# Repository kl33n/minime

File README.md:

# minime

3D printer mainboard Minime + Minime_mini, using a Raspberry Pi Pico (RP2040). Can be used on top of a Raspberry Pi or as standalone USB version.

The main goal of creating this little board was to design a 3D printer mainboard with Raspberry Pi Pico (RP2040) as MCU running Klipper firmware. Because of the limited number of I/O pins and ADC pins the board results in a very minimalistic (only 4 Stepper Driver on minime_mini) but also universal PCB.

Main Features:
- Running Klipper Firmware on Raspberry Pi Pico
- Raspberry Pi Host Version = use the minime and minime_mini as 3D Printer Mainboard with all primary features, like Heat_Bed and Hotend Control, Hotend Fan and Part Fan Control, X/Y/Z Endstop reading, Hotend Temperature and Bed Temperature reading, Probe reading, controlling 4 TMC2209 Stepper Driver
- The minime board can separately be used as standalone sensor board without the need of minime_mini as driver board and can directly be connected via usb to any Raspberry Pi Host
- Switchable between Endswitch and sensorless Homing via Solderjumper
- Switchable between +5V and +24V Probe via Solderjumper
- Switchable between +5V and +24V Fan Supply via Solderjumper
- Hotend Fan (Fan1, Sunon MF40100V1-1000C-G99) uses a 3 pin Header: VCC, GND and tachometer signal for savety reasons
- Fan tachometer signal can be set up in Klipper. If the speed of the Hotend Fan is not detectable, Klipper shuts down the printer (future option)
- Integrated bat85 diode (or similar) if using +24V probe
- Raspberry Pi Pico is used with pin headers to completely exchange the module if broken

Raspberry Pi Pico (with RP2040 Microcontroller):

- Raspberry Pi Host Version --> Raspberry Pi Pico has to be flashed with klipper.uf2 (UART Communication Option)
- Raspberry Pi Pico standalone Version --> Raspberry Pi Pico has to be flashed with klipper.uf2 (USB Communication Option)

A special thanks goes to Matt Shepcar (https://easyeda.com/matt_1626/) for his inspiring projects "Piglet print head control board" and "Raspberry Pi G-Code HAT"!

Future Modification:
- Switch from Raspberry Pi Pico Module to RP2040 integrated circuit
- Design two RP2040 MCU board, a host version with more than 4 stepper driver as driverboard and a separat sensorboard version including endswitches/hotend/bed/fans/temperatursensors and much more

Has to be continued!

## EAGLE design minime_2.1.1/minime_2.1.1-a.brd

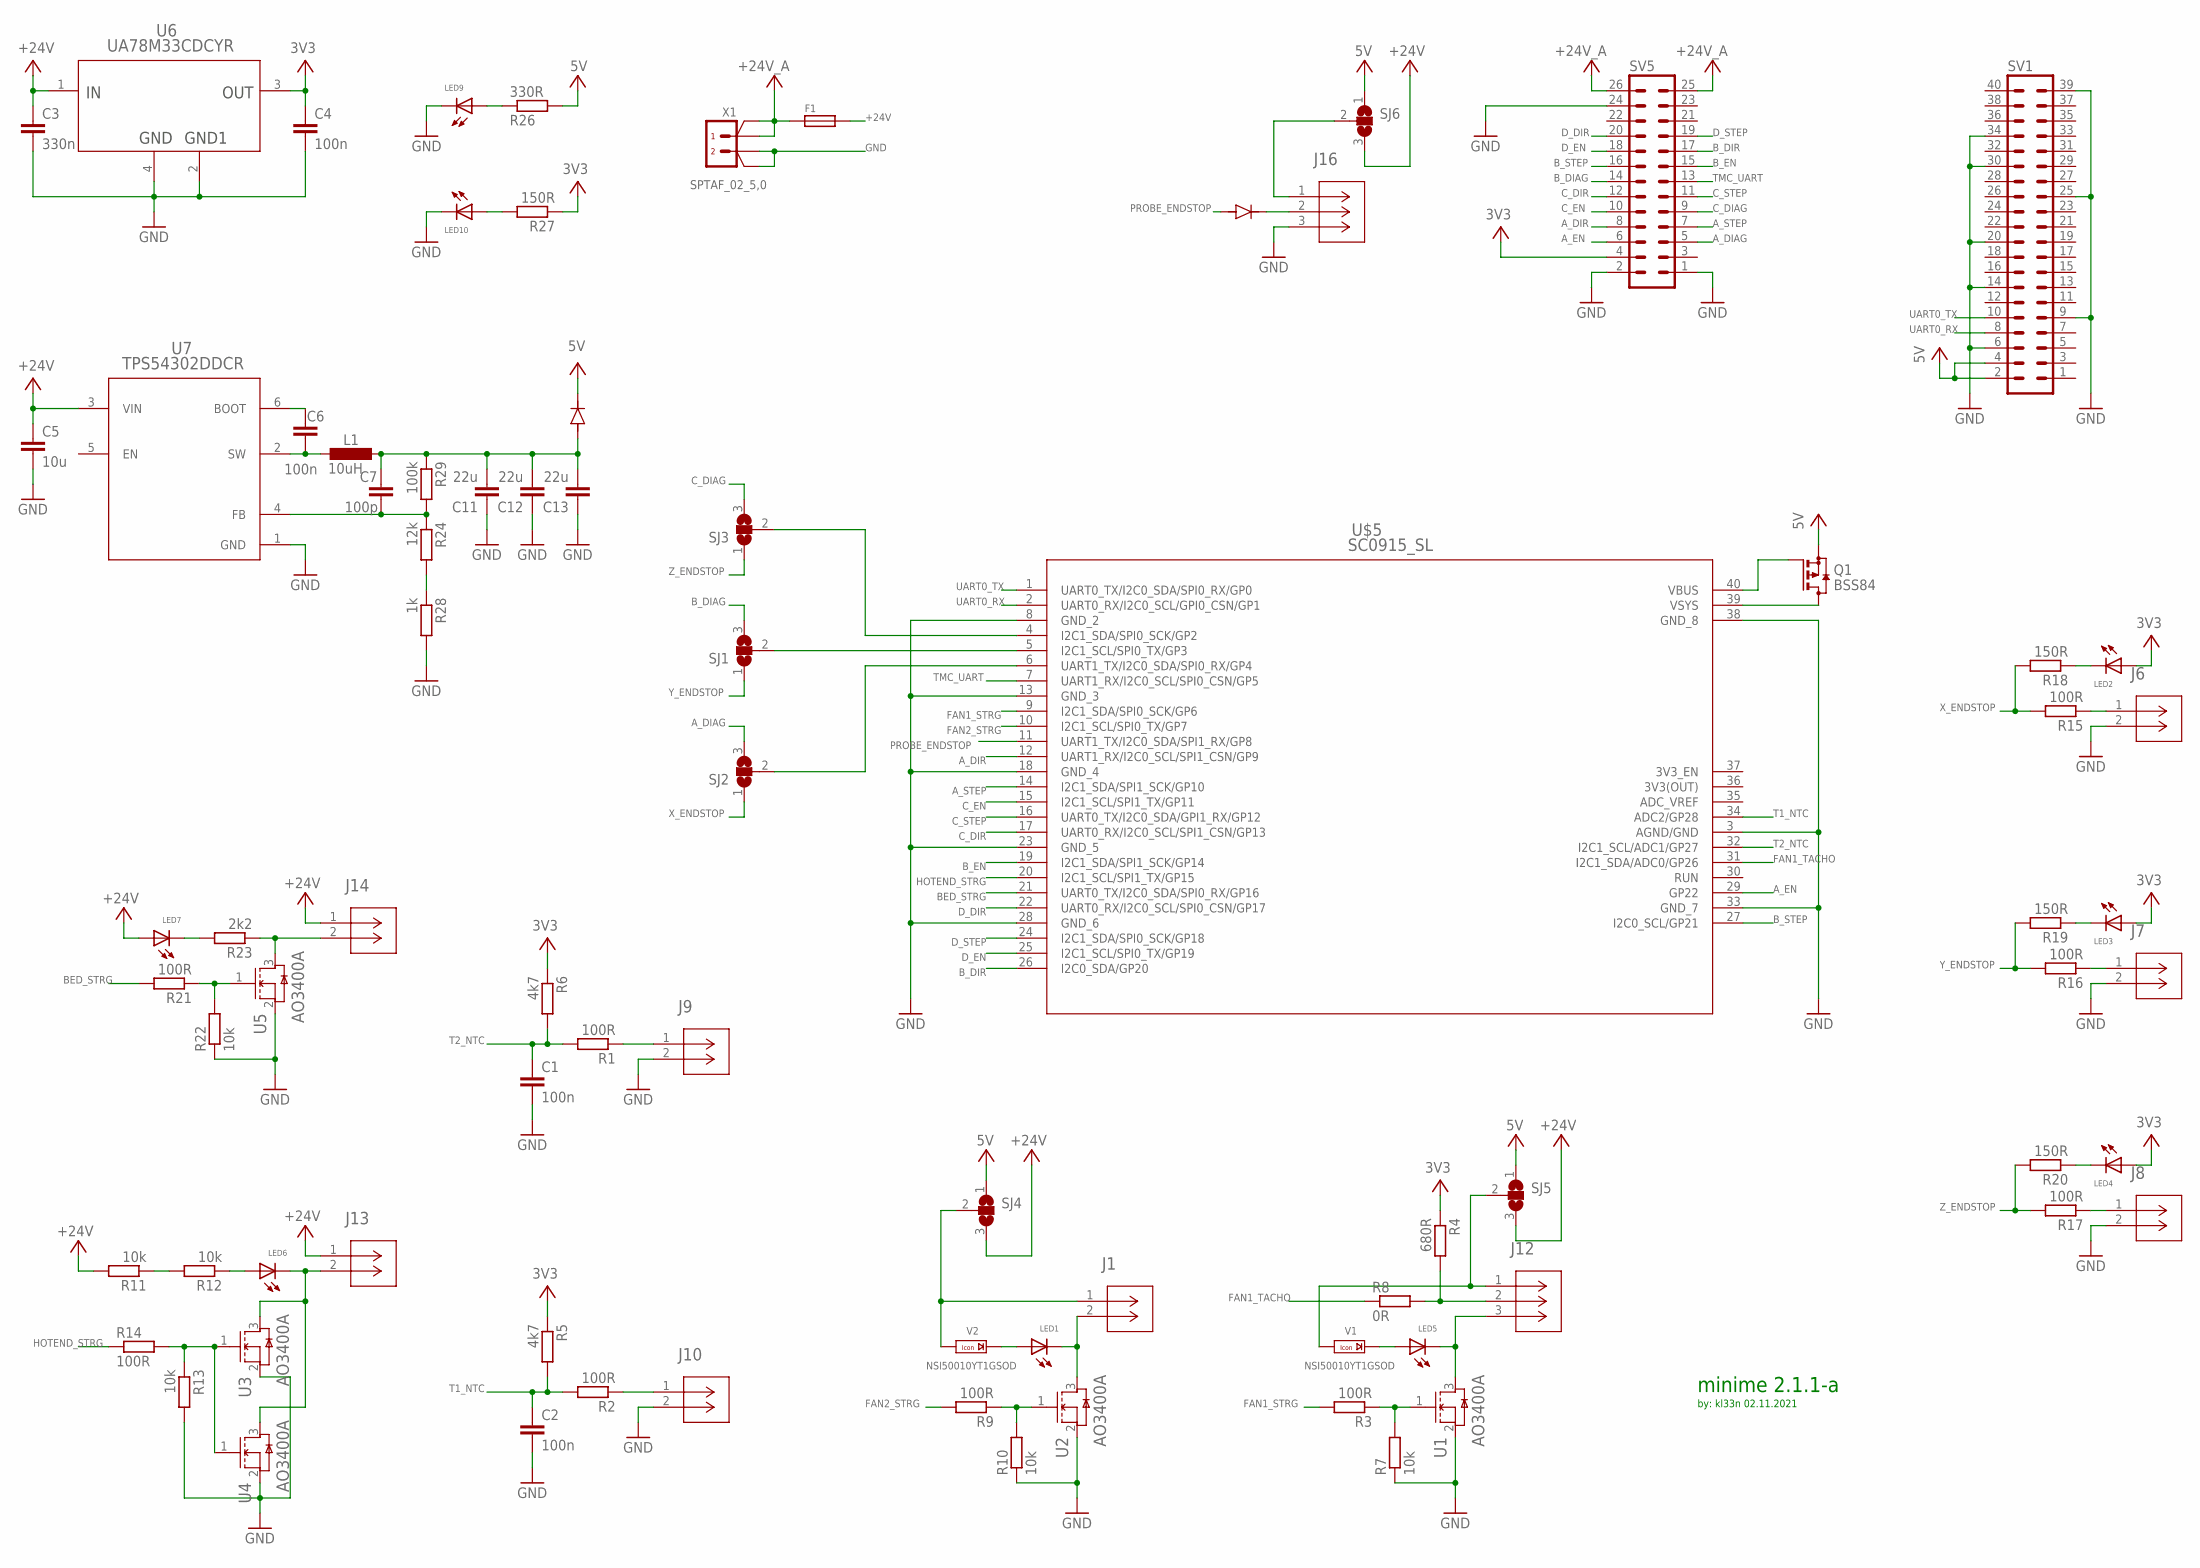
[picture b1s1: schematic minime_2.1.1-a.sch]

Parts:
C1, C2, C4, C6: 100n; C0603
C3: 330n; C0603
C5: 10u; C0603
C7: 100p; C0603
C11, C12, C13: 22u; C1210K
CR1: SS54; DIODE_DO214AC
CR2: SS14; DIODE_DO214AC
F1: FUSE/SERIE154; FUSE/NANO-OMNI
J1, J6, J7, J8, J9, J10, J13, J14: B2B-XH-A(LF)(SN); CONN_B2B-XH-A(LF)(SN)_JST
J12, J16: B3B-XH-A(LF)(SN); CONN_B3B-XH-A_JST
L1: 10uH; POWER-CHOKE_WE-TPC
LED1, LED2, LED3, LED4, LED5, LED6, LED7, LED9, LED10: LEDCHIP-LED0603; CHIP-LED0603
Q1: BSS84; SOT23
R1, R2, R3, R9, R14, R15, R16, R17, R21: 100R; R0603
R4: 680R; R0603
R5, R6: 4k7; R0603
R7, R10, R11, R12, R13, R22: 10k; R0603
R8: 0R; R0603
R18, R19, R20, R27: 150R; R0603
R23: 2k2; R0603
R24: 12k; R0603
R26: 330R; R0603
R28: 1k; R0603
R29: 100k; R0603
SJ1, SJ2, SJ3, SJ4, SJ5, SJ6: SJ2W; SJ_2
SV1: MA20-2
SV5: MA13-2
U1, U2, U3, U4, U5: AO3400A; SOT-23-3L_AOS
U6: UA78M33CDCYR; DCY0004A_N
U7: TPS54302DDCR; DDC0006A_N
U$5: SC0915_SL; STIFTLEISTE
V1, V2: NSI50010YT1GSOD; SOD123
X1: SPTAF_02_5,0; 5-2

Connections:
3V3: C4.1, LED2.A, LED3.A, LED4.A, R4.1, R5.1, R6.1, R27.1, SV5.4, U6.3 (OUTPUT)
3V3_EN: U$5.37 (3V3_EN)
5V: CR1.1, Q1.2 (S), R26.2, SJ4.1, SJ5.1, SJ6.1, SV1.2, SV1.4
+24V: C3.1, C5.1, F1.2, J13.1, J14.1, LED7.A, R11.2, SJ4.3, SJ5.3, SJ6.3, U6.1 (INPUT), U7.3 (VIN)
+24V_A: F1.1, SV5.25, SV5.26, X1.1, X1.1A
ADC_VREF: U$5.35 (ADC_VREF)
A_DIAG: SJ2.3, SV5.5
A_DIAG_X_ENDSTOP: SJ2.2, U$5.6 (UART1_TX/I2C0_SDA/SPI0_RX/GP4)
A_DIR: SV5.8, U$5.12 (UART1_RX/I2C0_SCL/SPI1_CSN/GP9)
A_EN: SV5.6, U$5.29 (GP22)
A_STEP: SV5.7, U$5.14 (I2C1_SDA/SPI1_SCK/GP10)
BED_STRG: R21.2, U$5.21 (UART0_TX/I2C0_SDA/SPI0_RX/GP16)
B_DIAG: SJ1.3, SV5.14
B_DIAG_Y_ENDSTOP: SJ1.2, U$5.5 (I2C1_SCL/SPI0_TX/GP3)
B_DIR: SV5.17, U$5.26 (I2C0_SDA/GP20)
B_EN: SV5.15, U$5.19 (I2C1_SDA/SPI1_SCK/GP14)
B_STEP: SV5.16, U$5.27 (I2C0_SCL/GP21)
C_DIAG: SJ3.3, SV5.9
C_DIAG_Z_ENDSTOP: SJ3.2, U$5.4 (I2C1_SDA/SPI0_SCK/GP2)
C_DIR: SV5.12, U$5.17 (UART0_RX/I2C0_SCL/SPI1_CSN/GP13)
C_EN: SV5.10, U$5.15 (I2C1_SCL/SPI1_TX/GP11)
C_STEP: SV5.11, U$5.16 (UART0_TX/I2C0_SDA/GPI1_RX/GP12)
D_DIR: SV5.20, U$5.22 (UART0_RX/I2C0_SCL/SPI0_CSN/GP17)
D_EN: SV5.18, U$5.25 (I2C1_SCL/SPI0_TX/GP19)
D_STEP: SV5.19, U$5.24 (I2C1_SDA/SPI0_SCK/GP18)
FAN1_STRG: R3.2, U$5.9 (I2C1_SDA/SPI0_SCK/GP6)
FAN1_TACHO: R8.1, U$5.31 (I2C1_SDA/ADC0/GP26)
FAN2_STRG: R9.2, U$5.10 (I2C1_SCL/SPI0_TX/GP7)
GND: C1.2, C2.2, C3.2, C4.2, C5.2, C11.1, C12.1, C13.1, J6.2, J7.2, J8.2, J9.2, J10.2, J16.3, LED9.C, LED10.C, R7.1, R10.1, R13.2, R22.1, R28.2, SV1.6, SV1.9, SV1.14, SV1.20, SV1.25, SV1.30, SV1.34, SV1.39, SV5.1, SV5.2, SV5.24, U1.2 (S), U2.2 (S), U3.2 (S), U4.2 (S), U5.2 (S), U6.2 (COMMON_2), U6.4 (COMMON), U7.1 (GND), U$5.3 (AGND/GND), U$5.8 (GND_2), U$5.13 (GND_3), U$5.18 (GND_4), U$5.23 (GND_5), U$5.28 (GND_6), U$5.33 (GND_7), U$5.38 (GND_8), X1.2, X1.2A
HOTEND_STRG: R14.1, U$5.20 (I2C1_SCL/SPI1_TX/GP15)
unnamed: LED6.A, R12.1
unnamed: R11.1, R12.2
unnamed: R21.1, R22.2, U5.1 (G)
unnamed: R13.1, R14.2, U3.1 (G), U4.1 (G)
unnamed: J16.1, SJ6.2
unnamed: LED5.A, V1.C (K)
unnamed: R9.1, R10.2, U2.1 (G)
unnamed: LED1.A, V2.C (K)
unnamed: J14.2, R23.1, U5.3 (D)
unnamed: J1.2, LED1.C, U2.3 (D)
unnamed: J8.1, R17.1
unnamed: J7.1, R16.1
unnamed: J6.1, R15.1
unnamed: J10.1, R2.1
unnamed: LED2.C, R18.1
unnamed: LED3.C, R19.1
unnamed: J9.1, R1.1
unnamed: J12.2, R4.2, R8.2
unnamed: LED4.C, R20.1
unnamed: R3.1, R7.2, U1.1 (G)
unnamed: LED7.C, R23.2
unnamed: J12.3, LED5.C, U1.3 (D)
unnamed: J13.2, LED6.C, U3.3 (D), U4.3 (D)
unnamed: LED9.A, R26.1
unnamed: J12.1, SJ5.2, V1.A
unnamed: LED10.A, R27.2
unnamed: J1.1, SJ4.2, V2.A
unnamed: CR2.1, J16.2
unnamed: R24.2, R28.1
unnamed: C6.1, U7.6 (BOOT)
unnamed: C6.2, L1.2, U7.2 (SW)
unnamed: C7.2, R24.1, R29.2, U7.4 (FB)
unnamed: C7.1, C11.2, C12.2, C13.2, CR1.2, L1.1, R29.1
PROBE_ENDSTOP: CR2.2, U$5.11 (UART1_TX/I2C0_SDA/SPI1_RX/GP8)
T1_NTC: C2.1, R2.2, R5.2, U$5.34 (ADC2/GP28)
T2_NTC: C1.1, R1.2, R6.2, U$5.32 (I2C1_SCL/ADC1/GP27)
TMC_UART: SV5.13, U$5.7 (UART1_RX/I2C0_SCL/SPI0_CSN/GP5)
UART0_RX: SV1.8, U$5.2 (UART0_RX/I2C0_SCL/GPI0_CSN/GP1)
UART0_TX: SV1.10, U$5.1 (UART0_TX/I2C0_SDA/SPI0_RX/GP0)
VBUS: Q1.1 (G), U$5.40 (VBUS)
VSYS: Q1.3 (D), U$5.39 (VSYS)
X_ENDSTOP: R15.2, R18.2, SJ2.1
Y_ENDSTOP: R16.2, R19.2, SJ1.1
Z_ENDSTOP: R17.2, R20.2, SJ3.1

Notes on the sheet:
by: kl33n 02.11.2021
minime 2.1.1-a

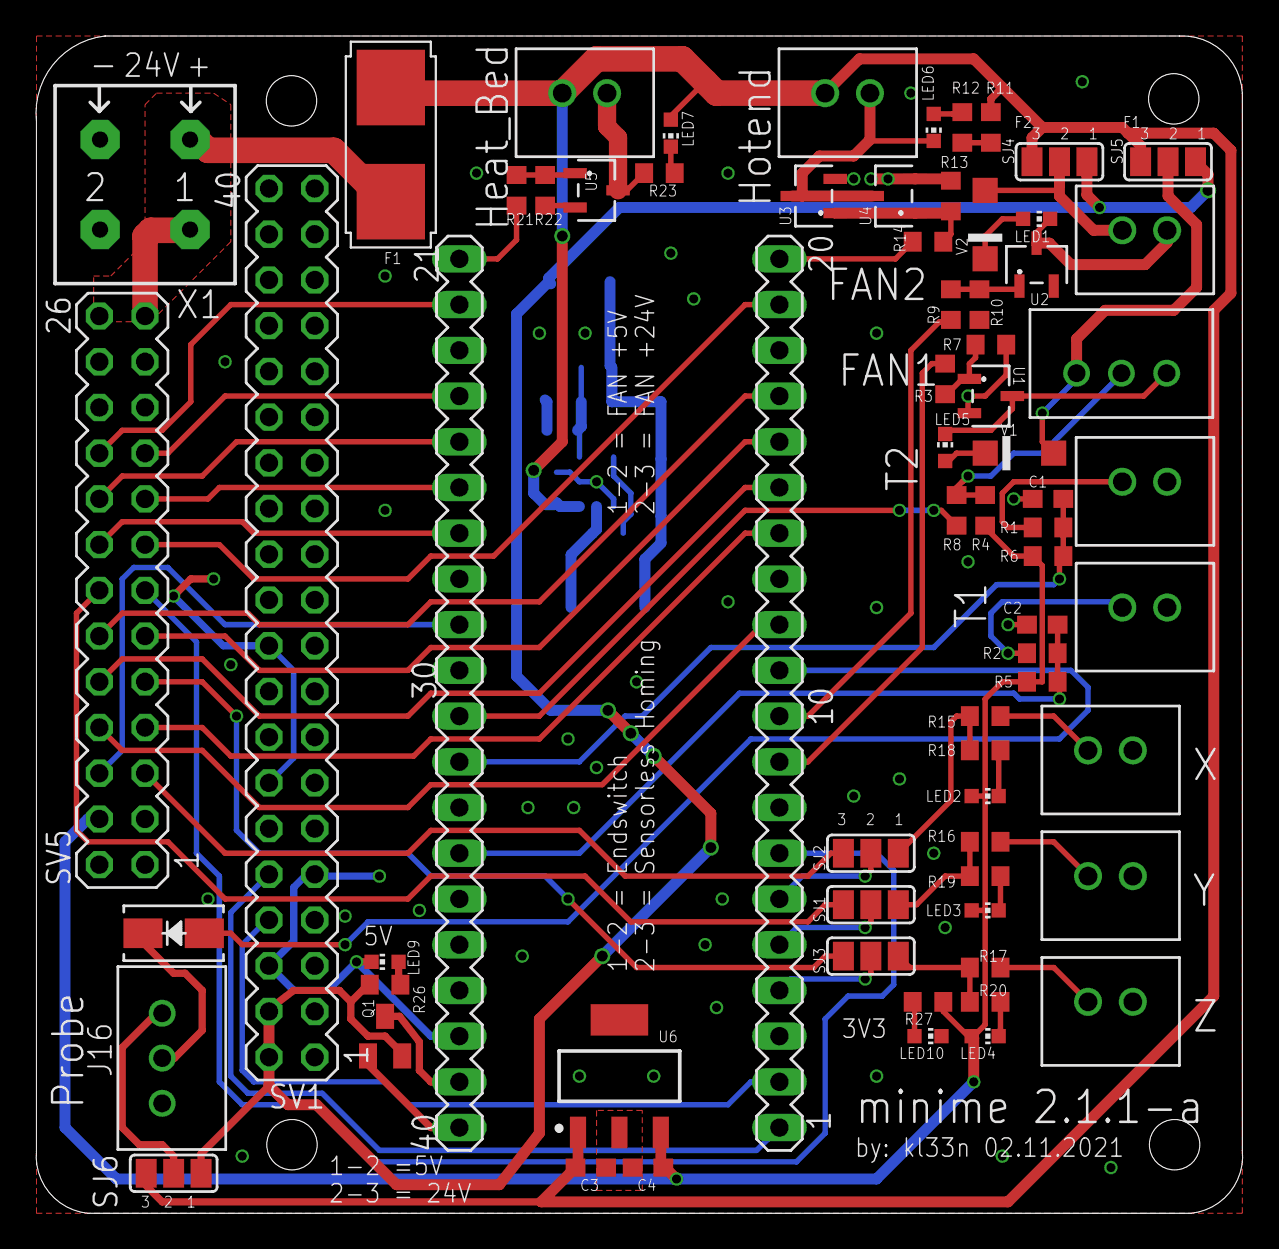
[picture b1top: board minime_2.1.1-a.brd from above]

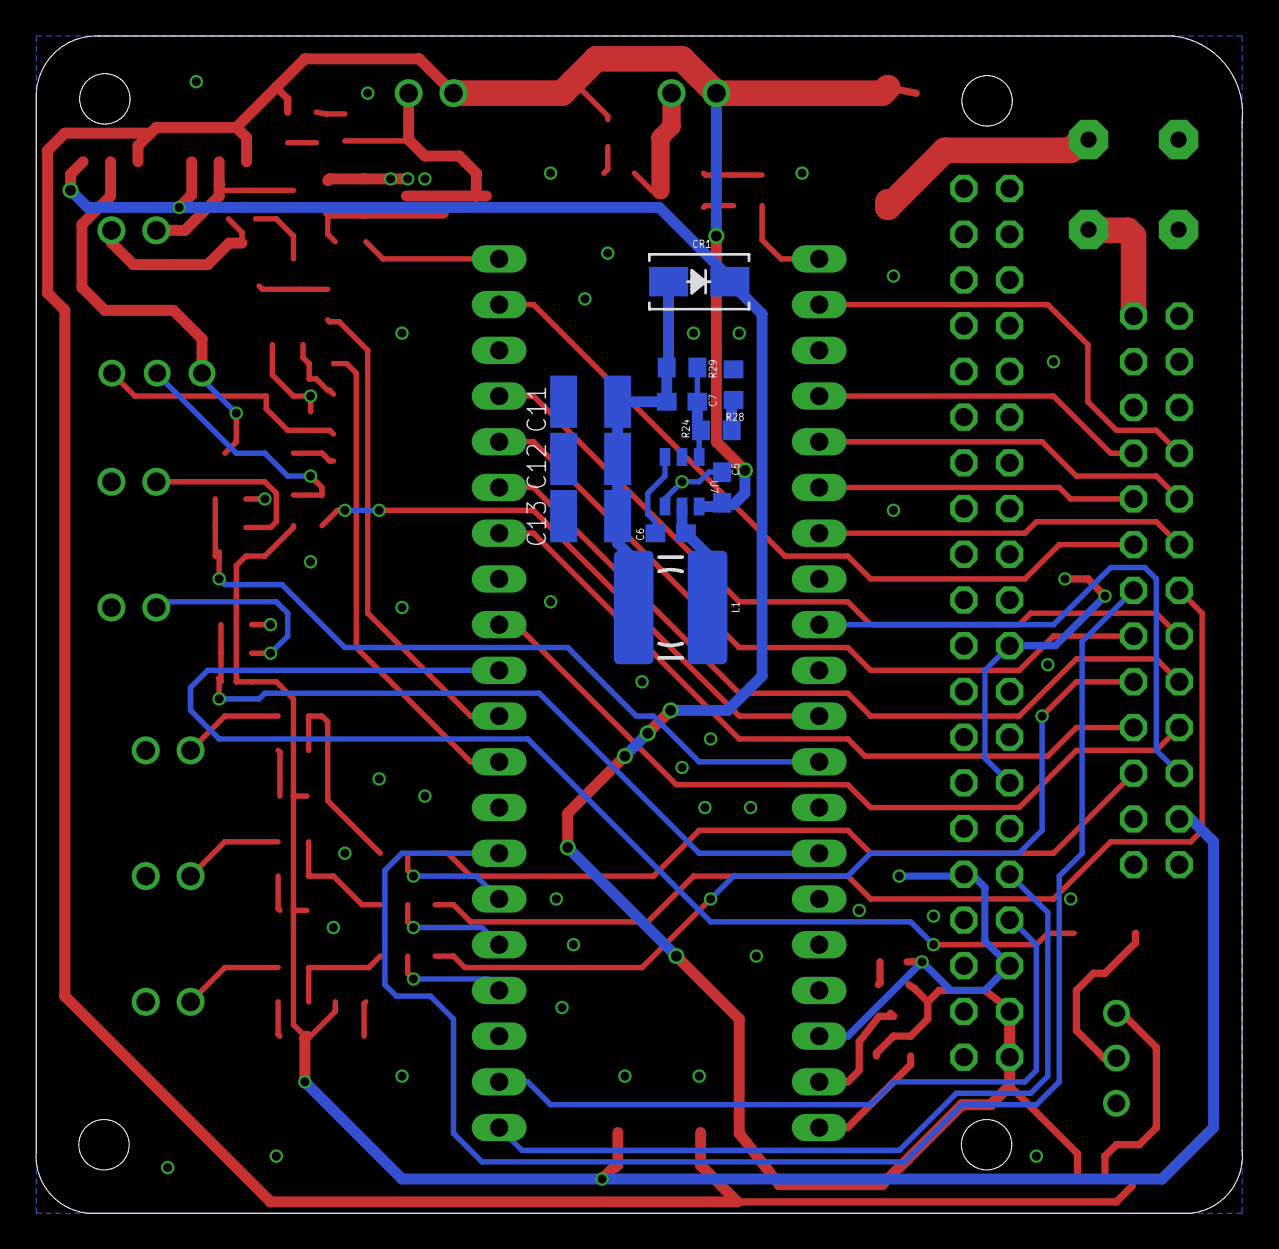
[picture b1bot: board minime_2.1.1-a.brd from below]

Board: 2 copper layers, 67.0 x 65.4 mm, 81 parts (12 on the bottom side), 72 nets.

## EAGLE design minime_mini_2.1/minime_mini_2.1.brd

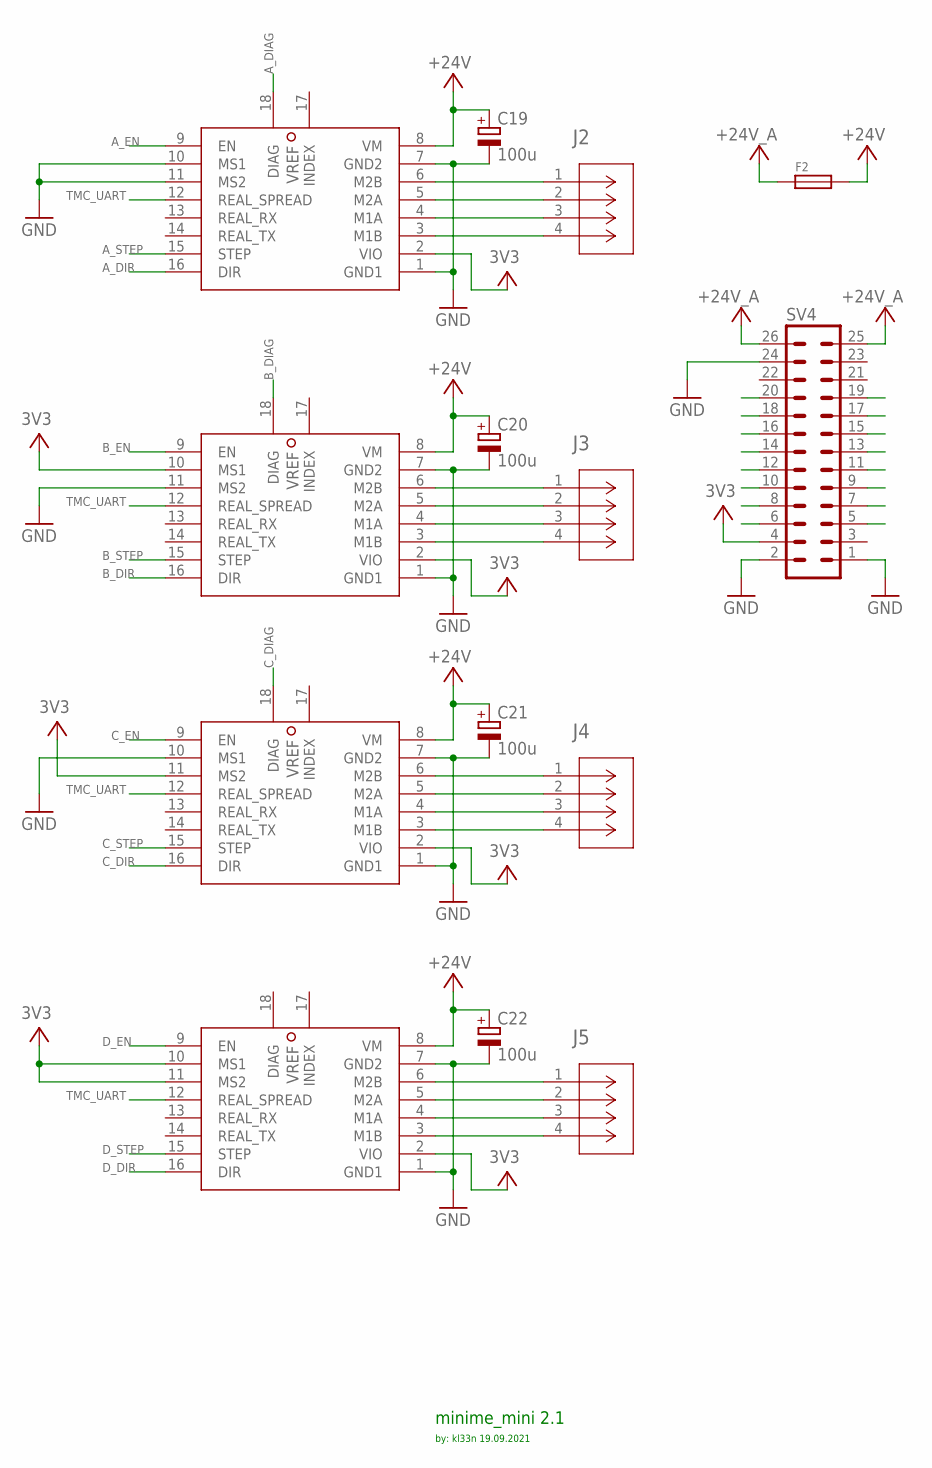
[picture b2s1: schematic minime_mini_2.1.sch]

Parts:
C19, C20, C21, C22: 100u; 175TMP-0810
F2: FUSE/SERIE154; FUSE/NANO-OMNI
J2, J3, J4, J5: B4B-XH-AM(LF)(SN); CONN_B4B-XH-AM_JST
SV4: MA13-2
U$1, U$2, U$3, U$4: TMC2209

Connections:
3V3: SV4.4, U$1.2 (VIO), U$1.10 (MS1), U$2.2 (VIO), U$3.2 (VIO), U$3.11 (MS2), U$4.2 (VIO), U$4.10 (MS1), U$4.11 (MS2)
+24V: C19.+, C20.+, C21.+, C22.+, F2.2, U$1.8 (VM), U$2.8 (VM), U$3.8 (VM), U$4.8 (VM)
+24V_A: F2.1, SV4.25, SV4.26
A_DIAG: SV4.5, U$2.18 (DIAG)
A_DIR: SV4.8, U$2.16 (DIR)
A_EN: SV4.6, U$2.9 (EN)
A_STEP: SV4.7, U$2.15 (STEP)
B_DIAG: SV4.14, U$1.18 (DIAG)
B_DIR: SV4.17, U$1.16 (DIR)
B_EN: SV4.15, U$1.9 (EN)
B_STEP: SV4.16, U$1.15 (STEP)
C_DIAG: SV4.9, U$3.18 (DIAG)
C_DIR: SV4.12, U$3.16 (DIR)
C_EN: SV4.10, U$3.9 (EN)
C_STEP: SV4.11, U$3.15 (STEP)
D_DIR: SV4.20, U$4.16 (DIR)
D_EN: SV4.18, U$4.9 (EN)
D_STEP: SV4.19, U$4.15 (STEP)
GND: C19.-, C20.-, C21.-, C22.-, SV4.1, SV4.2, SV4.24, U$1.1 (GND1), U$1.7 (GND2), U$1.11 (MS2), U$2.1 (GND1), U$2.7 (GND2), U$2.10 (MS1), U$2.11 (MS2), U$3.1 (GND1), U$3.7 (GND2), U$3.10 (MS1), U$4.1 (GND1), U$4.7 (GND2)
unnamed: J2.1, U$2.6 (M2B)
unnamed: J2.2, U$2.5 (M2A)
unnamed: J2.3, U$2.4 (M1A)
unnamed: J2.4, U$2.3 (M1B)
unnamed: J3.1, U$1.6 (M2B)
unnamed: J3.2, U$1.5 (M2A)
unnamed: J3.3, U$1.4 (M1A)
unnamed: J3.4, U$1.3 (M1B)
unnamed: J4.1, U$3.6 (M2B)
unnamed: J4.2, U$3.5 (M2A)
unnamed: J4.3, U$3.4 (M1A)
unnamed: J4.4, U$3.3 (M1B)
unnamed: J5.1, U$4.6 (M2B)
unnamed: J5.2, U$4.5 (M2A)
unnamed: J5.3, U$4.4 (M1A)
unnamed: J5.4, U$4.3 (M1B)
TMC_UART: SV4.13, U$1.12 (REAL_SPREAD), U$2.12 (REAL_SPREAD), U$3.12 (REAL_SPREAD), U$4.12 (REAL_SPREAD)

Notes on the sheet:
by: kl33n 19.09.2021
minime_mini 2.1

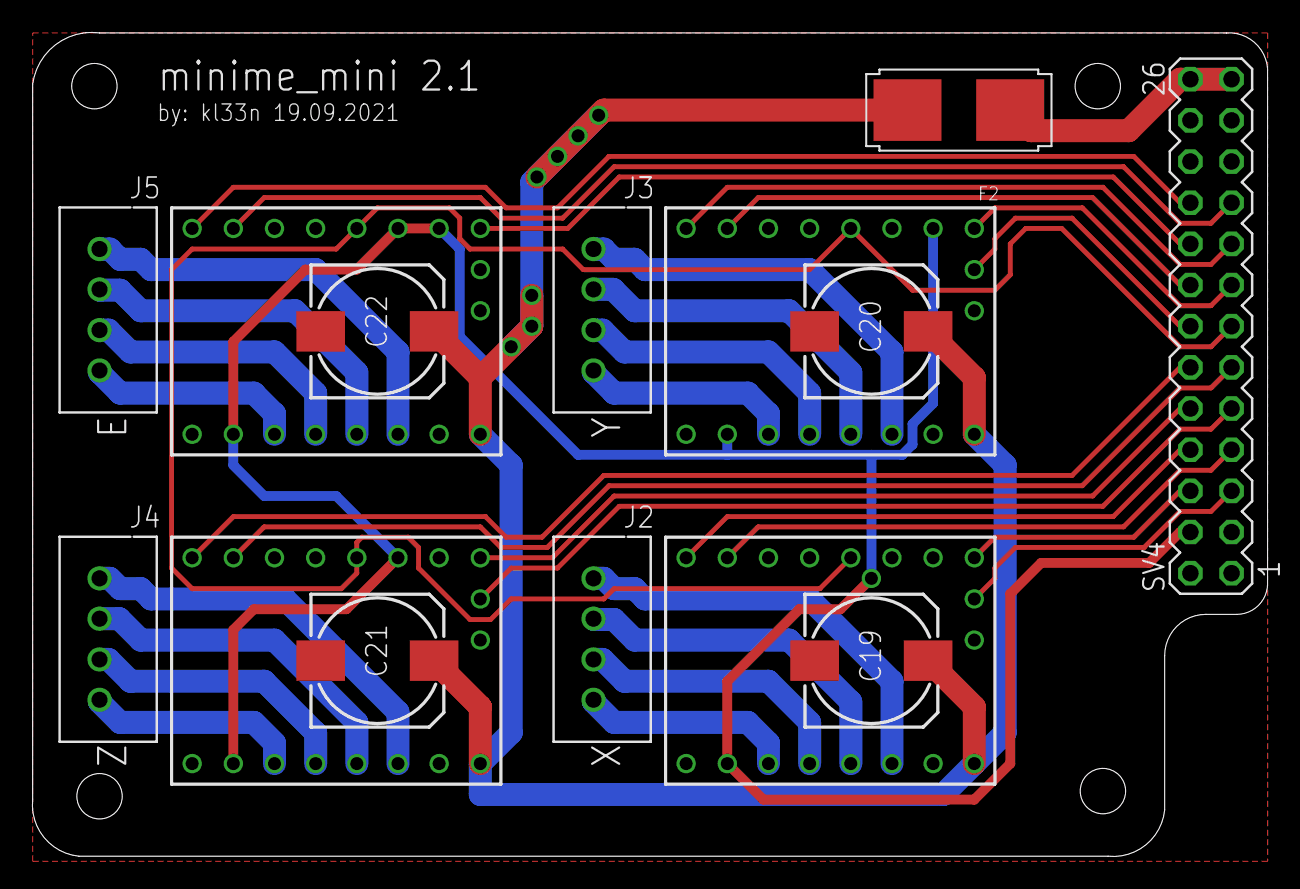
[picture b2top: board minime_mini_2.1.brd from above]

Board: 2 copper layers, 76.2 x 50.8 mm, 14 parts (0 on the bottom side), 36 nets.

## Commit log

2021-10-11 new dir structure
2021-10-21 minime_2.1.1
2021-10-21 removed Archive
2021-11-02 new version 2.1.1-a
2021-11-02 removed docs
2021-11-02 new doc minime_2.1.1_a
2021-11-02 minime_2.1.1-a
2021-11-02 add Manufacturing Files

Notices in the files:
parts and their libraries:
COPYRIGHT: Copyright (C) 2018 Accelerated Designs. All rights reserved
COPYRIGHT: Copyright (C) 2021 Ultra Librarian. All rights reserved.
